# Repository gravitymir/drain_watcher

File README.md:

# drain_watcher

Логгер тока утечки автомобильного аккумулятора: шунт в минусе аккумулятора,
плата-датчик на INA228 снимает с него напряжение и отдаёт замеры по I2C внешнему
контроллеру (ESP32 и т.п.). Контроллер питается от пауэрбанка, поднимает точку доступа
Wi-Fi и отдаёт веб-страницу с историей.

- [`hardware/`](hardware/) — плата KiCad 10 (схема, разводка, гербера, BOM/CPL для JLCPCB)
  и скрипты, которые её собирают. Подробности — в [hardware/README.md](hardware/README.md).
- [`firmware/ina228/`](firmware/ina228) — драйвер датчика на Rust, `no_std`, поверх
  `embedded-hal 1.0`. Без привязки к контроллеру: ему нужна только шина I2C, так что
  он одинаково встанет и в ESP-IDF, и в голый `esp-hal`.
- Прошивка контроллера (ESP32, Wi-Fi AP и веб-страница с историей) — будет здесь же.

## Драйвер INA228

Главное, ради чего он написан, — два диапазона по шунту и корректный переход между ними.
Ток утечки живёт в десятках миллиампер, и узкая шкала даёт по нему вчетверо лучшее
разрешение; подробности и цифры — в [hardware/README.md](hardware/README.md#измерение-два-диапазона-и-калибровка).

```rust
use ina228::{Ina228, Range, DEFAULT_ADDRESS};

// Шунт 2.5 мОм, верх шкалы 35 А. Стартуем на узкой шкале — машина спит.
let mut sensor = Ina228::new(i2c, DEFAULT_ADDRESS, 0.0025, 35.0);
sensor.init(Range::Narrow)?;

loop {
    // Сам уйдёт на широкую шкалу, если блок проснулся, и вернётся обратно.
    let m = sensor.measure_autoranged()?;
    log(m.current_a, m.bus_v, m.die_c);
}
```

`set_range` переписывает `SHUNT_CAL` вместе с `ADCRANGE` — поменять одно без другого
через этот API нельзя, а именно так и получается тихая ошибка в четыре раза.

Сборка и тесты:

```bash
cd firmware/ina228 && cargo test
```

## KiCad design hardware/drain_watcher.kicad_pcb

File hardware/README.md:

# drain_watcher: плата v3

Логгер тока утечки автомобильного аккумулятора: ESP32-S3 и INA228 на одной плате. Питается
от того же аккумулятора через понижающий преобразователь, Wi-Fi поднимает сама: история
замеров смотрится с телефона или ноутбука через веб-страницу, без проводов к машине.

Шунт стоит на силовых шинах в минусе аккумулятора, **основной ток по плате не идёт**: она
только снимает напряжение с шунта (четырёхпроводное подключение, Kelvin) и напряжение
аккумулятора.

| | |
|---|---|
| Размер | 52 × 41.2 мм, без крепёжных отверстий, 2 слоя, 1.6 мм, медь 1 oz |
| Контроллер | ESP32-S3-WROOM-1-N8R2 (металлический экран, до +85 °C), антенна у левого края |
| Измерение | INA228 (20 бит, смещение ±1 мкВ), I2C, адрес **0x40** (A0 = A1 = GND) |
| Звук | I2S-микрофон ICS-43434, моно |
| Питание | BAT+ 6…24 В (AP63205, 5 В) **или** USB-C 5 В; 3.3 В — TLV75733 |
| Проверки | DRC KiCad 10: 0 нарушений на всех уровнях, схема = плата; ERC: 0 сообщений |

## Провода J2 — к шунту и аккумулятору

Четыре отверстия 1.15 мм под провод до 0.5 мм², шаг 4.6 мм. Провода впаиваются наглухо.

| Контакт | Цепь | Куда |
|---|---|---|
| 1 `SNS+` | SNS_P | измерительный винт шунта со стороны **кузова** (отдельный тонкий провод) |
| 2 `SNS-` | SNS_N | измерительный винт шунта со стороны **аккумулятора** (отдельный тонкий провод) |
| 3 `GND` | GND | та же сторона шунта, что и SNS-, но **своим** проводом |
| 4 `BAT+` | VBAT | плюс аккумулятора через **предохранитель 1 А в самом проводе** |

SNS+ и SNS- скрутите в пару и заведите прямо на измерительные винты шунта. Положительный
ток означает разряд. BAT+ теперь и питает плату (ESP32 с Wi-Fi — в среднем ~40 мА от 12 В,
пики ~150 мА), и даёт INA228 напряжение аккумулятора.

## Выводы ESP32

| Сигнал | GPIO | Вывод модуля |
|---|---|---|
| I2C SDA (INA228) | IO13 | 21 |
| I2C SCL (INA228) | IO12 | 20 |
| ALERT INA228 | IO21 | 23 — подтяжки на плате нет, включите внутреннюю |
| RGB-светодиод WS2812B (DIN) | IO48 | 25 — как на DevKitC-1 |
| Кнопка BOOT | IO0 | 27 |
| USB D-/D+ | IO19/IO20 | 13/14 — встроенный USB Serial/JTAG: прошивка и логи |
| Микрофон I2S SD | IO47 | 24 — данные, подтяжка 100 кОм на землю (R12) на плате |
| Микрофон I2S WS | IO14 | 22 |
| Микрофон I2S SCK | IO11 | 19 |

Подтяжки I2C 4.7 кОм к 3.3 В стоят на плате.

### Микрофон

**MK1 — ICS-43434** (I2S MEMS, как в Voice-Unit) в середине верхней части, над INA228.
Развязка C11 100 нФ вплотную к выводу VDD. R12 100 кОм держит линию SD на земле, пока
микрофон её отпускает (так требует даташит).
Вывод L/R на земле — левый канал, моно. Звуковой порт у него снизу: под корпусом в плате
отверстие 0.5 мм, звук заходит с **обратной стороны** — в корпусе напротив него нужно
отверстие. В прошивке: I2S, 24 бита в 32-битном слове, левый канал, частота до 48 кГц.

### Ряд отверстий GPIO (J3, шаг 2.54 мм)

Над модулем, слева направо (подписи с обеих сторон):

`IO1 IO2 TX RX IO42 IO41 IO40 IO39 IO38 IO37 IO36 IO35 GND 3V3 5V`

Это все свободные выводы верхнего ряда модуля в том же порядке, что и у самого модуля.
IO35–IO37 свободны только у модулей **без восьмибитной PSRAM** (N8, N8R2). У N16R8 они
заняты памятью, поэтому такой модуль сюда не ставить. `5V` — общая шина после диодов
«ИЛИ» (~4.6 В), `3V3` — выход стабилизатора, от каждого можно взять до ~200 мА.

## Питание

```
BAT+ ─ D4 (B5819W) ─┬─ D5 SMF24A, C10 10 мкФ ─ U3 AP63205 ─ L1 4.7 мкГн ─ C13,C14 2×22 мкФ ─ D6 ─┐
                    (VIN, до 32 В)                                       (+5V_B)                ├─ +5V ─ U4 TLV75733 ─ +3V3
USB VBUS ────────────────────────────────────────────────────────────────────────── D7 ────────┘
```

- **D4** — защита от переполюсовки BAT+ (Шоттки, теряется ~0.4 В).
- **D5** — TVS 24 В от выбросов на входе. Машина при замерах не заводится, выше 14.4 В
  напряжение не поднимается, запас до предела AP63205 (32 В) большой.
- **D6, D7** — диоды «ИЛИ»: плата одинаково работает от аккумулятора, от USB или от
  обоих сразу, и USB-порт компьютера не получает напряжение с преобразователя.
- **USB-C** — для прошивки и логов. Подключённый к машине, компьютер оказывается
  соединённым с кузовом через GND. Ноутбук на батарее — нормально, компьютер от сети —
  нет (или через USB-изолятор).

## Шунт

Плата рассчитана на замеры **на заглушённой машине**: двигатель не запускается, машина не
едет. Тогда весь ток — это блоки, свет и вентиляторы, максимум ~20–25 А, с запасом **35 А**.

| | |
|---|---|
| Шунт | четырёхвыводной, **30 А / 75 мВ = 2.5 мОм** (например CG FL-2C 30A 75mV, класс 0.5) |
| Шкала | широкий диапазон ±163.84 мВ — до ~65 А; узкий ±40.96 мВ — до ~16 А с шагом ~31 мкА |
| Точность на утечке | ±0.4 мА по смещению INA228, после калибровки нуля — порядка ±0.05–0.1 мА |

**Запуск двигателя через шунт на 2.5 мОм недопустим**: 150–300 А его сожгут, а сгоревший в
обрыв шунт оставит машину без основной массы. Поставьте **параллельно шунту выключатель
массы** на 100–300 А: замкнут — шунт закорочен, машина ездит как обычно; разомкнут — идёт
замер.

## Измерение: два диапазона и калибровка

У INA228 полная шкала по шунту переключается битом **`ADCRANGE`** в регистре `CONFIG`.
Те же 20 бит ложатся на вчетверо меньший диапазон, то есть шаг становится вчетверо мельче:

| `ADCRANGE` | полная шкала | шаг по напряжению | на шунте 2.5 мОм |
|---|---|---|---|
| 0 — широкий | ±163.84 мВ | 312.5 нВ | до ±65 А, шаг 125 мкА |
| 1 — узкий | ±40.96 мВ | 78.125 нВ | до ±16 А, **шаг 31 мкА** |

Ток утечки — десятки миллиампер: 30 мА на 2.5 мОм дают 75 мкВ, то есть почти тысячу
отсчётов на узкой шкале и всего две с половиной сотни на широкой. Поэтому спящая машина
меряется узким диапазоном, а широкий нужен, только когда какой-то блок проснулся и утянул
больше ~16 А.

**При смене диапазона обязательно пересчитывается `SHUNT_CAL`.** Он считается как
`13107.2e6 × CURRENT_LSB × R_шунта`, и для узкого диапазона результат **умножается на 4**.
В драйвере [`firmware/ina228`](../firmware/ina228) диапазон меняется только через
`set_range`, который сразу переписывает и `SHUNT_CAL`, а `measure_autoranged` сам уходит в
широкую шкалу при переполнении узкой и возвращается, когда ток опустится ниже 80 % узкой.

**Параметры для прошивки:** `R_SHUNT = 0.0025` Ом, верх шкалы 35 А, отсюда
`CURRENT_LSB = 35 / 2¹⁹ ≈ 66.8 мкА`. Один раз — калибровка нуля (замкнуть SNS+ и SNS− и
запомнить смещение) и коэффициента (сверка с мультиметром или токовыми клещами). Делитель
VBUS занижает напряжение примерно на 1 % — тоже калибровочный коэффициент.

## Вход измерения

- **Ток**: TVS SMF24CA (двунаправленный) на проводах, затем по 10 Ом в каждую линию и
  100 нФ между входами у INA228 (как в TI, раздел 8.1).
- **Напряжение АКБ**: 10 кОм (1206) → SMF24A на землю + 100 нФ → VBUS INA228.
- **TVS на входе 24 В, а не ±5 В.** Входы INA228 выдерживают ±40 В дифференциально и
  85 В синфазно, ток в вывод — до 5 мА. TVS на 5 В при случайном касании SNS+ к +12 В
  открылся бы и замкнул аккумулятор через провод. SMF24CA при 12 В закрыт.
- **VBUS через 10 кОм** ограничивает ток при переполюсовке до 1.2 мА (меньше 5 мА).

## Заказ

JLCPCB, три файла из этой папки:

1. **`drain_watcher_gerbers.zip`** — плата. 2 слоя, FR-4, 1.6 мм, медь 1 oz, остальное по
   умолчанию. Дорожки от 0.15 мм (у падов USB-C — 0.13 мм), зазоры 0.2 мм, отверстия от 0.3 мм, via 0.6/0.3 — всё в
   стандартных нормах для двухслойки.
2. **`BOM.csv`** — 38 SMD-деталей, номера LCSC проставлены. ESP32-S3, INA228, AP63205,
   TLV75733, WS2812B, ICS-43434, B5819W, дроссель, USB-C, кнопки и TVS — Extended (разовая плата за
   установку каждой позиции), пассивка — Basic. **Наличие проверьте при заказе**: INA228
   сейчас в дефиците (см. ниже).
3. **`pos.csv`** — координаты для монтажа (только верхняя сторона).

В просмотрщике размещения у JLCPCB проверьте:
- **U1** (модуль) — антенна к левому краю платы, за контур;
- **U2, U3, U4** — точка/ключ первого вывода — как на шелкографии;
- **D4, D6, D7, D2, D5** — полоска катода как на шелкографии;
- **D3** (WS2812B) — скошенный угол/метка 1-го вывода как на шелкографии.

Поправки для JLCPCB уже внесены в `pos.csv` (`ROT_FIX` и `POS_FIX` в `gen/export.py`):
U2, U3, U4 и микрофон MK1 — +270°, у них корпус в библиотеке EasyEDA лежит поперёк; модуль U1 — +3.62 мм
по X, у EasyEDA начало координат модуля в центре падов; USB-C J1 — 1.57 мм по Y.
Проверка — `gen/jlc_check.py`: она скачивает посадочные места JLCPCB по номерам LCSC и
сравнивает их пады с нашими (`~` у кнопок, D1 и центрального пада модуля — норма).

J2 (провода) и J3 (ряд GPIO) — только отверстия: в BOM и CPL их нет.

**ICS-43434** (C5656610) снят с производства, остатки на складе небольшие. Если его не
окажется — «Do not place» и запаять руками (корпус LGA 3.5 × 2.65 мм, только феном).

**INA228** у JLCPCB/LCSC, DigiKey и Mouser сейчас нет (ожидается в 2027). Вариант —
выпаять из модулей Adafruit 5832 и поставить руками (MSOP-10), а в BOM исключить U2.
По выводам совместим INA226 (16 бит, шкала ±81.92 мВ) — подходит как временная замена.

## Сборка из скриптов

Плату не рисовали мышкой: схему, размещение, ручную разводку критичных цепей и шелк
описывает `gen/build.py`, остальное разводит Freerouting через `gen/route.py`, после чего
углы скругляются дугами. Нужен Python из KiCad 10, а для перетрассировки — Java 21+ и
[Freerouting 2.5](https://github.com/freerouting/freerouting/releases) (переменные
`JAVA` и `FREEROUTING_JAR`, по умолчанию `~/tools/jre/*/bin/java` и
`~/tools/freerouting/freerouting-2.5.0.jar`).

```bash
sh gen/check.sh
```

Скрипт пересобирает схему и плату, разводит её и прогоняет DRC KiCad с проверкой схемы
против платы, ERC, зазоры, связность, courtyard и шелк. Выходные файлы для заказа:

```bash
"/c/Program Files/KiCad/10.0/bin/python.exe" gen/outputs.py drain_watcher.kicad_pcb
"/c/Program Files/KiCad/10.0/bin/python.exe" gen/export.py .
```

### Как устроена разводка

- **Вручную** (`build.py`, заблокирована): Kelvin-пара от проводов через RC-фильтр к
  INA228, VBUS INA228, земля адреса, BAT+ → D4, via на землю у силовой части.
- **Freerouting** (`route.py`): всё остальное, только углы 45°, питание 0.4–0.5 мм, USB
  0.15 мм. У узких падов USB-C роутер сам сужает дорожку, `route.py` доводит такие места
  до 0.13 мм (норма JLCPCB для двухслойки — от 0.127). Результат (`drain_watcher.ses`) лежит в репозитории вместе с ключом
  (`.ses.key`). Пока не менялись детали, их места и ручная разводка, роутер не
  запускается, плата собирается из готового `.ses` одинаково. `--reroute` — развести
  заново.
- **Правило проекта** `drain_watcher.kicad_dru`: мелким земляным падам со своей
  дорожкой на via (адрес INA228, земля микрофона) хватает одной тепловой перемычки к
  заливке.
- **Дуги**: каждый излом заменяется дугой радиусом до 1 мм; если дуга подошла к
  соседу ближе зазора, она откатывается обратно в излом.
- Freerouting от раза к разу разводит по-разному. Если DRC KiCad результат не
  пропускает, `route.py` разводит заново (до 8 попыток).

Версии без контроллера (модуль INA228 под внешний ESP32) и прошлые варианты с ESP32
остались в истории git.

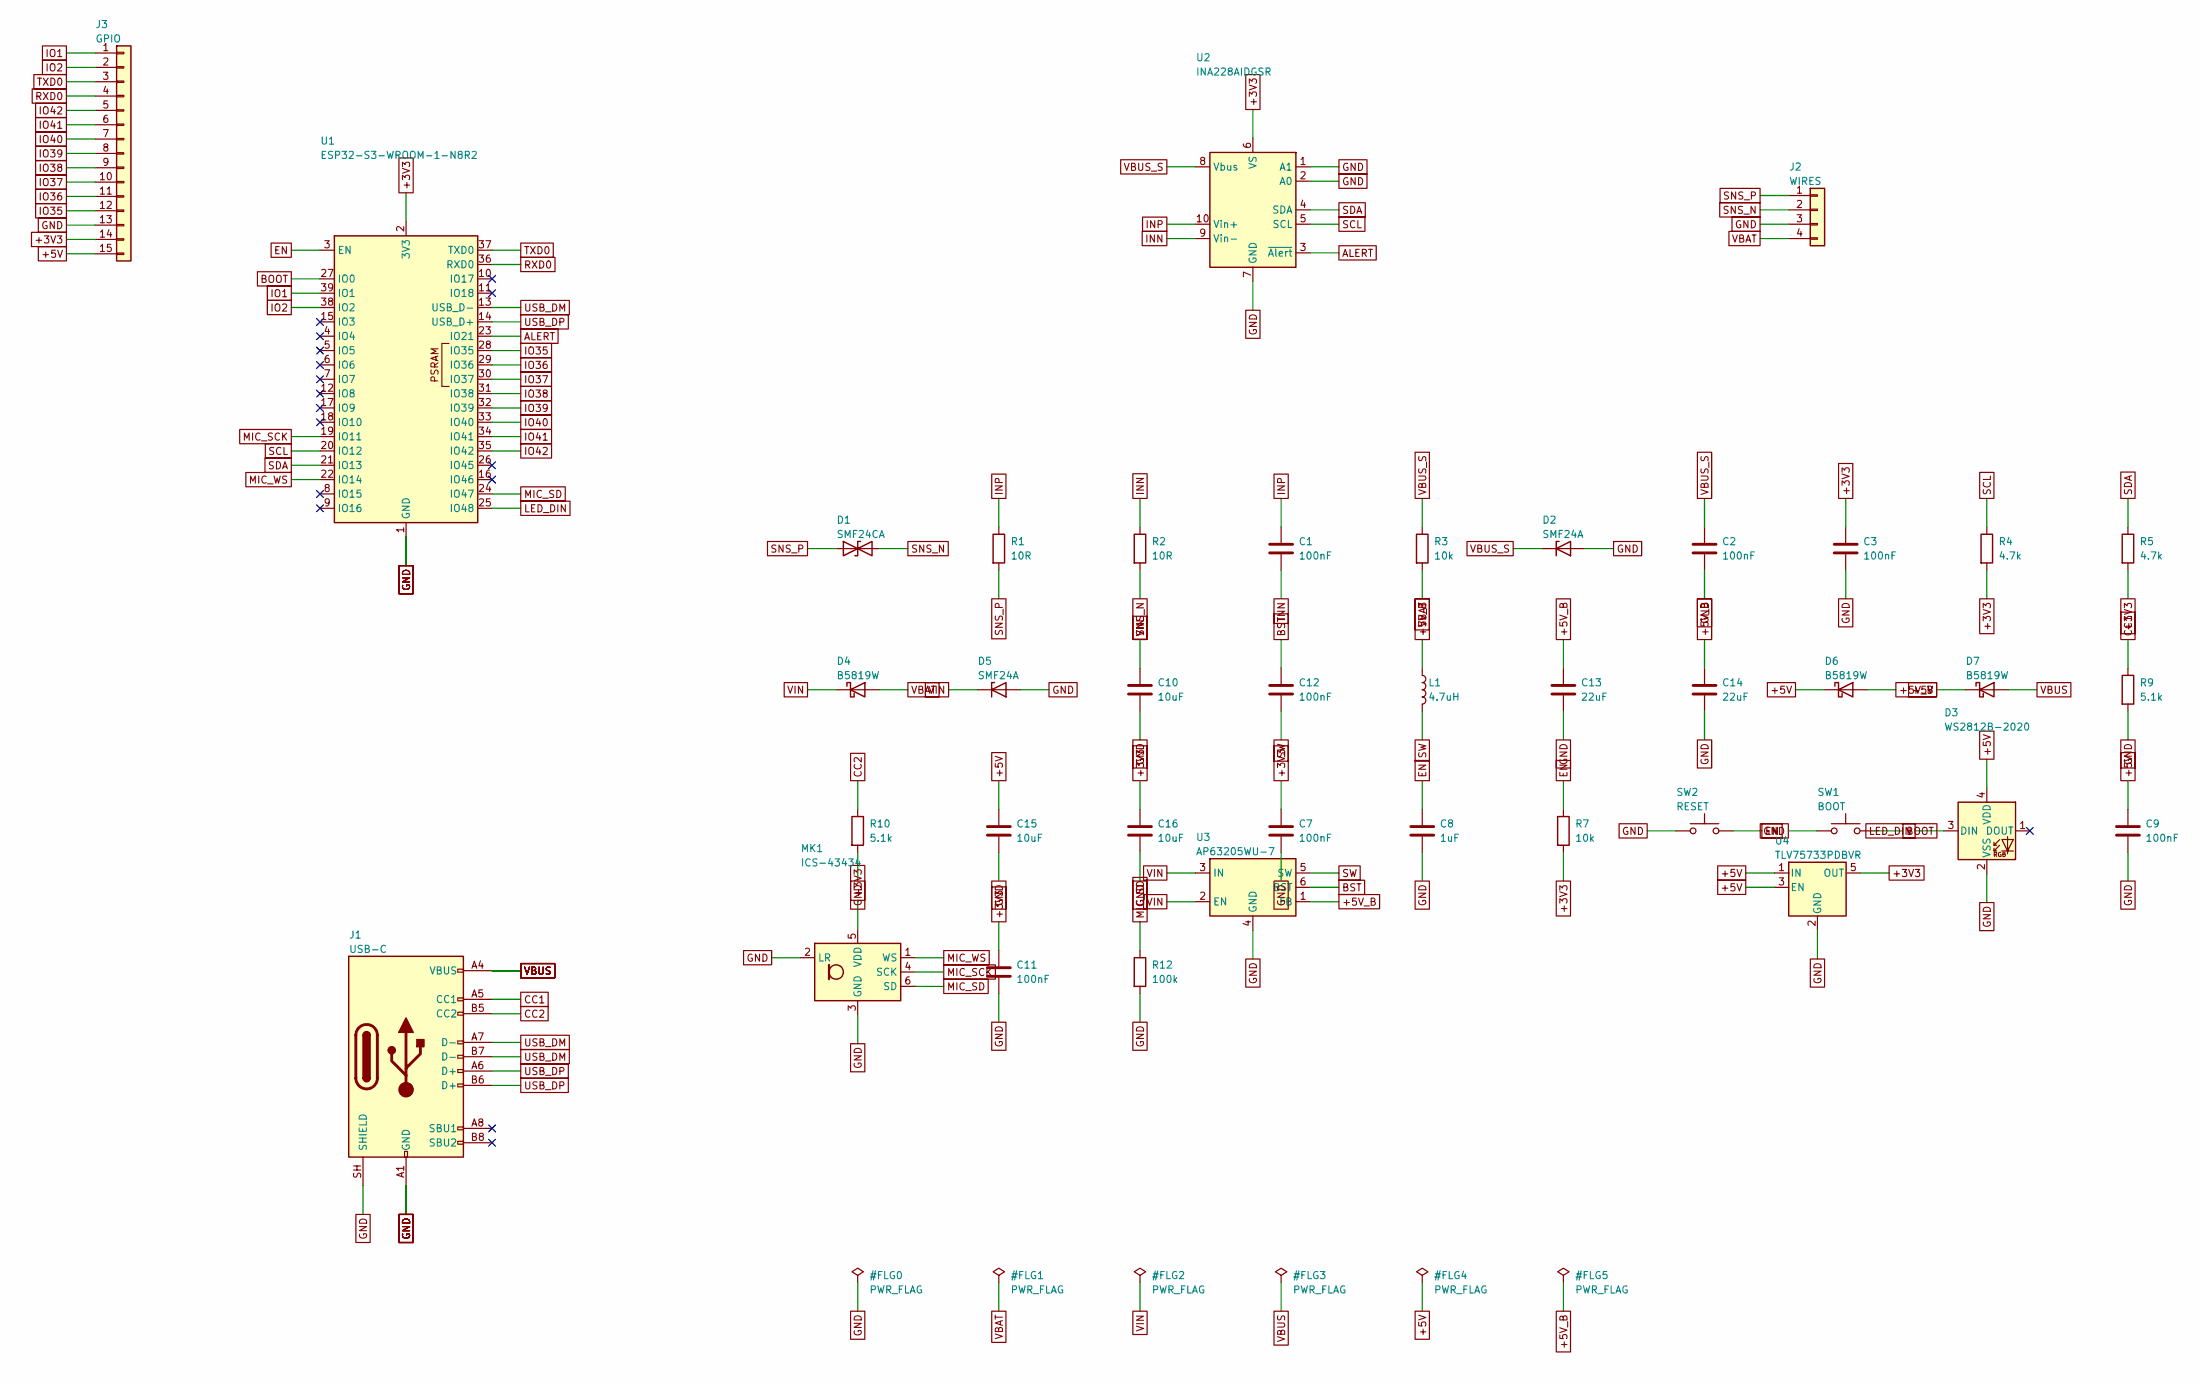
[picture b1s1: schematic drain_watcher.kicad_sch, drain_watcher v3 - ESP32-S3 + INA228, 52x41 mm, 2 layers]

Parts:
C1, C2, C3, C7, C9, C11, C12: 100nF; C_0603_1608Metric
C8: 1uF; C_0603_1608Metric
C10, C15, C16: 10uF; C_0805_2012Metric
C13, C14: 22uF; C_0805_2012Metric
D1: SMF24CA; D_SOD-123F
D2, D5: SMF24A; D_SOD-123F
D3: WS2812B-2020; LED_WS2812B-2020_PLCC4_2.0x2.0mm
D4, D6, D7: B5819W; D_SOD-123
J1: USB-C; USB_C_Receptacle_HRO_TYPE-C-31-M-12
J2: WIRES; SolderWire-0.5sqmm_1x04_P4.6mm_D0.9mm_OD2.1mm
J3: GPIO; PinHeader_1x15_P2.54mm_Vertical
L1: 4.7uH; L_Sunlord_SWPA4030S
MK1: ICS-43434; InvenSense_ICS-43434-6_3.5x2.65mm
R1, R2: 10R; R_0603_1608Metric
R3: 10k; R_1206_3216Metric
R4, R5: 4.7k; R_0603_1608Metric
R7: 10k; R_0603_1608Metric
R9, R10: 5.1k; R_0603_1608Metric
R12: 100k; R_0603_1608Metric
SW1: BOOT; SW_Push_1P1T_XKB_TS-1187A
SW2: RESET; SW_Push_1P1T_XKB_TS-1187A
U1: ESP32-S3-WROOM-1-N8R2; ESP32-S3-WROOM-1
U2: INA228AIDGSR; MSOP-10_3x3mm_P0.5mm
U3: AP63205WU-7; TSOT-23-6
U4: TLV75733PDBVR; SOT-23-5

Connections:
+3V3: C3.1, C7.1, C11.1, C16.1, J3.14, MK1.5 (VDD), R4.2, R5.2, R7.2, U1.2 (3V3), U2.6 (VS), U4.5 (OUT)
+5V: C9.1, C15.1, D3.4 (VDD), D6.1 (K), D7.1 (K), J3.15, U4.1 (IN), U4.3 (EN)
+5V_B: C13.1, C14.1, D6.2 (A), L1.1, U3.1 (FB)
ALERT: U1.23 (IO21), U2.3 (~Alert)
BOOT: SW1.2, U1.27 (IO0)
BST: C12.1, U3.6 (BST)
CC1: J1.A5 (CC1), R9.1
CC2: J1.B5 (CC2), R10.1
EN: C8.1, R7.1, SW2.2, U1.3 (EN)
GND: C2.2, C3.2, C7.2, C8.2, C9.2, C10.2, C11.2, C13.2, C14.2, C15.2, C16.2, D2.2 (A), D3.2 (VSS), D5.2 (A), J1.A1 (GND), J1.A12 (GND), J1.B1 (GND), J1.B12 (GND), J1.SH (SHIELD), J2.3, J3.13, MK1.2 (LR), MK1.3 (GND), R9.2, R10.2, R12.2, SW1.1, SW2.1, U1.1 (GND), U1.40 (GND), U1.41 (GND), U2.1 (A1), U2.2 (A0), U2.7 (GND), U3.4 (GND), U4.2 (GND)
INN: C1.2, R2.1, U2.9 (Vin-)
INP: C1.1, R1.1, U2.10 (Vin+)
IO1: J3.1, U1.39 (IO1)
IO2: J3.2, U1.38 (IO2)
IO35: J3.12, U1.28 (IO35)
IO36: J3.11, U1.29 (IO36)
IO37: J3.10, U1.30 (IO37)
IO38: J3.9, U1.31 (IO38)
IO39: J3.8, U1.32 (IO39)
IO40: J3.7, U1.33 (IO40)
IO41: J3.6, U1.34 (IO41)
IO42: J3.5, U1.35 (IO42)
LED_DIN: D3.3 (DIN), U1.25 (IO48)
MIC_SCK: MK1.4 (SCK), U1.19 (IO11)
MIC_SD: MK1.6 (SD), R12.1, U1.24 (IO47)
MIC_WS: MK1.1 (WS), U1.22 (IO14)
RXD0: J3.4, U1.36 (RXD0)
SCL: R4.1, U1.20 (IO12), U2.5 (SCL)
SDA: R5.1, U1.21 (IO13), U2.4 (SDA)
SNS_N: D1.2 (A2), J2.2, R2.2
SNS_P: D1.1 (A1), J2.1, R1.2
SW: C12.2, L1.2, U3.5 (SW)
TXD0: J3.3, U1.37 (TXD0)
USB_DM: J1.A7 (D-), J1.B7 (D-), U1.13 (USB_D-)
USB_DP: J1.A6 (D+), J1.B6 (D+), U1.14 (USB_D+)
VBAT: D4.2 (A), J2.4, R3.2
VBUS: D7.2 (A), J1.A4 (VBUS), J1.A9 (VBUS), J1.B4 (VBUS), J1.B9 (VBUS)
VBUS_S: C2.1, D2.1 (K), R3.1, U2.8 (Vbus)
VIN: C10.1, D4.1 (K), D5.1 (K), U3.2 (EN), U3.3 (IN)

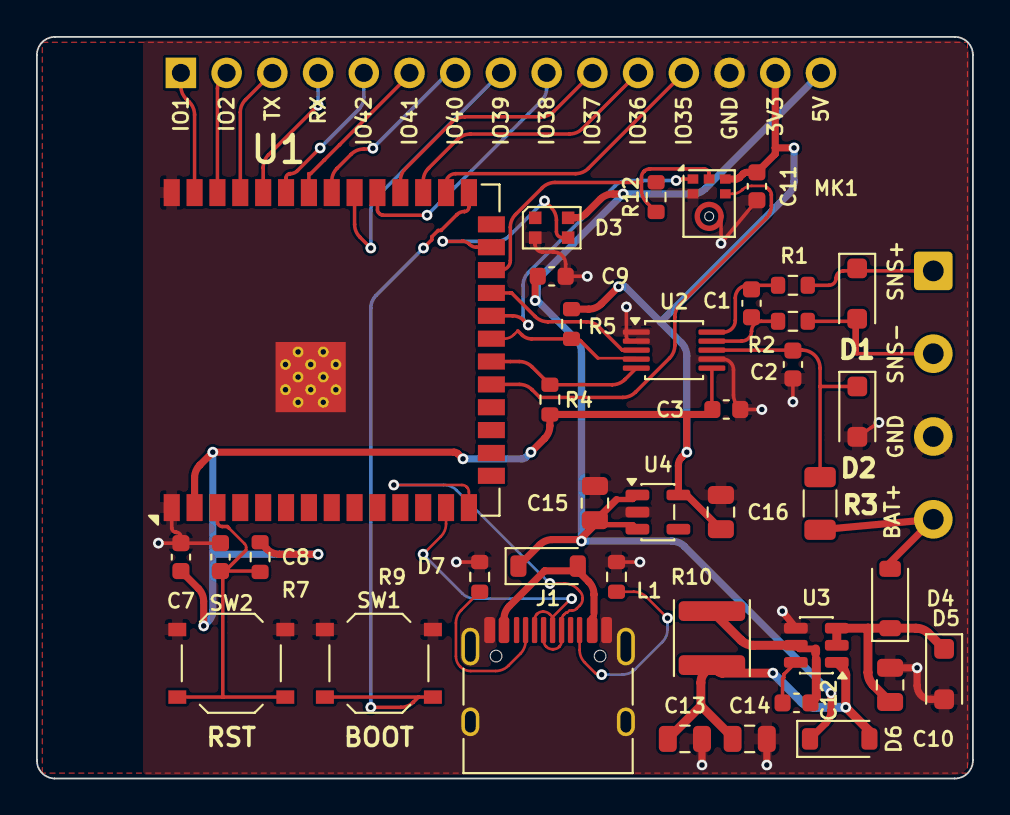
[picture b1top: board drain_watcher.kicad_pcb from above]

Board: 2 copper layers, 52.0 x 41.2 mm, 40 parts (0 on the bottom side), 39 nets.

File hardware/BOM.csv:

Comment,Designator,Footprint,LCSC Part #,Qty,Note
100nF,"C1,C11,C12,C2,C3,C7,C9",drain_watcher:C_0603_1608Metric,C14663,7,проверить наличие на складе
1uF,C8,drain_watcher:C_0603_1608Metric,C15849,1,проверить наличие на складе
10uF,"C10,C15,C16",drain_watcher:C_0805_2012Metric,C15850,3,проверить наличие на складе
22uF,"C13,C14",drain_watcher:C_0805_2012Metric,C45783,2,проверить наличие на складе
B5819W,"D4,D6,D7",drain_watcher:D_SOD-123,C8598,3,проверить наличие на складе; любой Шоттки 40 В 1 А в SOD-123 (SS14 в SMA не встанет)
SMF24A,"D2,D5",drain_watcher:D_SOD-123F,C3035828,2,проверить наличие на складе
SMF24CA,D1,drain_watcher:D_SOD-123F,C3035829,1,проверить наличие на складе
ESP32-S3-WROOM-1-N8R2,U1,drain_watcher:ESP32-S3-WROOM-1,C2913204,1,проверить наличие на складе; подойдёт ESP32-S3-WROOM-1-N8 (C2913198); N16R8 - нет: восьмибитная PSRAM занимает IO35-IO37
ICS-43434,MK1,drain_watcher:InvenSense_ICS-43434-6_3.5x2.65mm,C5656610,1,"проверить наличие на складе; снят с производства (EOL), склад мал - проверить; иначе не ставить и паять вручную"
WS2812B-2020,D3,drain_watcher:LED_WS2812B-2020_PLCC4_2.0x2.0mm,C965555,1,проверить наличие на складе
4.7uH,L1,drain_watcher:L_Sunlord_SWPA4030S,C57269,1,проверить наличие на складе
INA228AIDGSR,U2,drain_watcher:MSOP-10_3x3mm_P0.5mm,C2887910,1,проверить наличие на складе
10R,"R1,R2",drain_watcher:R_0603_1608Metric,C22859,2,проверить наличие на складе
4.7k,"R4,R5",drain_watcher:R_0603_1608Metric,C23162,2,проверить наличие на складе
5.1k,"R10,R9",drain_watcher:R_0603_1608Metric,C23186,2,проверить наличие на складе
100k,R12,drain_watcher:R_0603_1608Metric,C25803,1,проверить наличие на складе
10k,R7,drain_watcher:R_0603_1608Metric,C25804,1,проверить наличие на складе
10k,R3,drain_watcher:R_1206_3216Metric,C17902,1,проверить наличие на складе
TLV75733PDBVR,U4,drain_watcher:SOT-23-5,C485517,1,проверить наличие на складе
BOOT/RESET,"SW1,SW2",drain_watcher:SW_Push_1P1T_XKB_TS-1187A,C318884,2,проверить наличие на складе
AP63205WU-7,U3,drain_watcher:TSOT-23-6,C2071056,1,проверить наличие на складе
USB-C,J1,drain_watcher:USB_C_Receptacle_HRO_TYPE-C-31-M-12,C165948,1,проверить наличие на складе
